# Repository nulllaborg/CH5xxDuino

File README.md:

# CH5xxDuino-Nano
本项目是基于https://github.com/DeqingSun/ch55xduino 项目修改而成

硬件原理图如下

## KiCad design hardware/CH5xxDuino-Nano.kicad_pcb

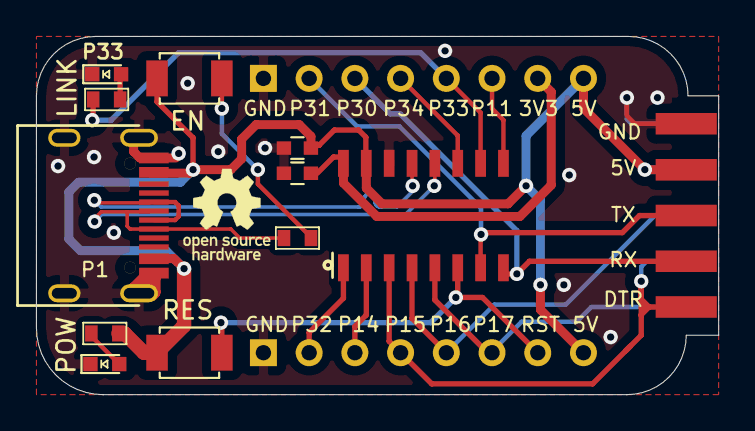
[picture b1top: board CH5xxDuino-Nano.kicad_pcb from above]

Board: 2 copper layers, 37.9 x 19.9 mm, 14 parts (1 on the bottom side), 19 nets.

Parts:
C1: 0.1uF; C_0603
D1, D2: LED; LED_0603
JP1, JP2: PIN8; DIP-1.5Hole-2.54mm-Pitch-8P
JP3: JACK5*2; SMD_CONN_5P
P1: USB_C_Plug_USB2.0; C393939
R6: 20K; R_0603
R7, R8: 1K; R_0603
SW1: RST; SW_SPST_B3U-1000P
SW2: BOOT; SW_SPST_B3U-1000P
U1: CH552G; SOIC-16_3.9x9.9mm_Pitch1.27mm
e: 0.1uF; C_0603

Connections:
+3V3: JP1.7, U1.16, e.1
+5V: C1.1, JP1.8, JP2.8, JP3.2, JP3.9, P1.A4, R8.2, SW1.1, SW2.1, U1.15
/D+: P1.A6, R6.1, U1.12
/D-: P1.A7, U1.13
/DTR&RST: JP2.4, JP3.4, JP3.6, U1.3
/LINK: JP1.5, R7.2, U1.10
/P11: JP1.6, U1.9
/P14: JP2.3, U1.2
/P16: JP2.5, JP3.3, U1.4
/P17: JP2.6, JP3.5, U1.5
/P30: JP1.3, JP3.7, U1.8
/P31: JP1.2, JP3.8, U1.7
/P32: JP2.2, U1.1
/P34: JP1.4, U1.11
/RST: JP2.7, SW1.2, U1.6
GND: C1.2, D1.1, D2.1, JP1.1, JP2.1, JP3.1, JP3.10, P1.A1, P1.S1, U1.14, e.2
unnamed: D1.2, R7.1
unnamed: D2.2, R8.1
unnamed: R6.2, SW2.2

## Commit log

2022-04-17 Add hardware
2022-04-22 Review CH5xxDuino Hardware
2022-05-05 update 3d shapes
